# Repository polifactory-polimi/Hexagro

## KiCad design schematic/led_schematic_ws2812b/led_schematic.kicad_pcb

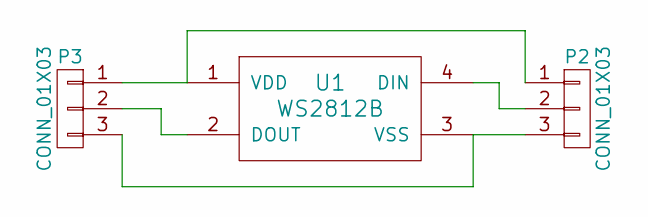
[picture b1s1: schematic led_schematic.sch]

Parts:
P2, P3: CONN_01X03; Pin_Header_Straight_1x03
U1: WS2812B; PLCC4-5050

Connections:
unnamed: P2.1, P3.1, U1.1 (VDD)
unnamed: P2.2, U1.4 (DIN)
unnamed: P2.3, P3.3, U1.3 (VSS)
unnamed: P3.2, U1.2 (DOUT)

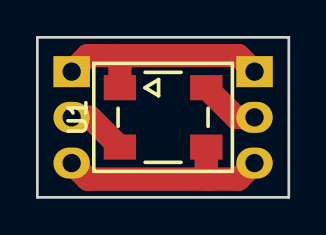
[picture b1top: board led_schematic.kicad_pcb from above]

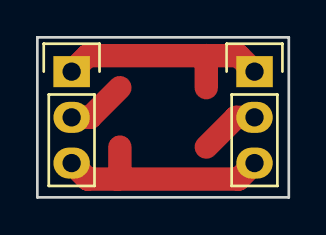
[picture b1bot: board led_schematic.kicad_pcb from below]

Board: 2 copper layers, 14.0 x 8.9 mm, 3 parts (2 on the bottom side), 4 nets.

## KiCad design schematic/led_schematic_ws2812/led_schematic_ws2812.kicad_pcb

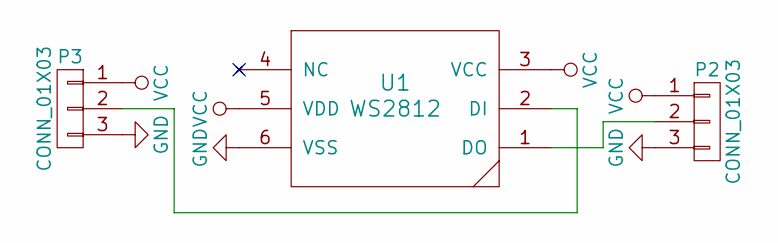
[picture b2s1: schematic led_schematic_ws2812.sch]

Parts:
P2, P3: CONN_01X03; Pin_Header_Straight_1x03
U1: WS2812; PLCC6-SM-RGB-LED

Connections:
GND: P2.3, P3.3, U1.6 (VSS)
unnamed: P2.2, U1.1 (DO)
unnamed: P3.2, U1.2 (DI)
VCC: P2.1, P3.1, U1.3 (VCC), U1.5 (VDD)

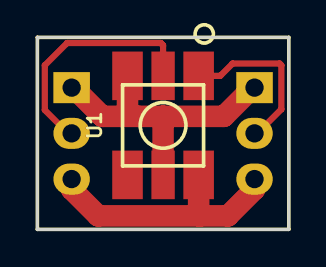
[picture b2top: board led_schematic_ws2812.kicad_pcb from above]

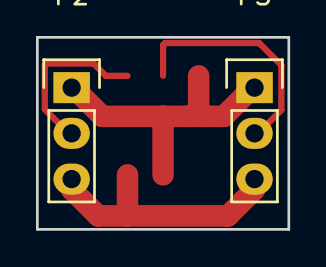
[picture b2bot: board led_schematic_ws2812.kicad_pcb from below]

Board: 2 copper layers, 14.0 x 10.7 mm, 3 parts (2 on the bottom side), 4 nets.
